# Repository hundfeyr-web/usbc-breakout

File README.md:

# USB-C to 3.3 V Breakout

A small 2-layer breakout board designed in KiCad. It takes 5 V from a USB-C port and gives a regulated 3.3 V on a 3-pin header.

This is the first design I've posted. It has not been fabricated or tested, and I don't plan to build it, so feedback on the design is welcome (see [Status](#status)).

## Features

- USB-C receptacle input (USB 2.0, 16-pin)
- 5.1 kΩ resistors on CC1 and CC2 so a USB-C charger supplies 5 V
- AP2112K-3.3 LDO regulator with input and output capacitors
- 3-pin header: +5V, +3V3, GND
- 30 x 25 mm, 2 layers, GND copper pour on both layers

## Bill of materials

| Ref | Value | Part | Qty |
|-----|-------|------|-----|
| J1 | USB-C receptacle | Palconn UTC16-G (16-pin, USB 2.0) | 1 |
| U1 | 3.3 V LDO | AP2112K-3.3 (SOT-23-5) | 1 |
| C1, C2 | 1 µF | Capacitor (C1 input, C2 output) | 2 |
| C3 | 100 nF | Output capacitor | 1 |
| R1, R2 | 5.1 kΩ | CC1 and CC2 resistors | 2 |
| J2 | 1x03 | Pin header (+5V, +3V3, GND) | 1 |

## Files

- `*.kicad_pro`, `*.kicad_sch`, `*.kicad_pcb`: KiCad project, schematic and board
- `images/`: 3D renders
  - `usbc-breakout.png`: top view
  - `2.png`: front view
  - `3.png` and `4.png`: side views
  - `5.png`: back view

## Design notes

- **Connector:** J1 is rotated 180° so its "PCB Edge" line sits on the top board edge.
- **Symbol and footprint mismatch:** my first USB-C connector symbol did not match the footprint, which caused a pile of DRC errors. Switching to the 16-pin Palconn UTC16-G symbol and footprint fixed it.
- **Ground fill:** GND zones on F.Cu and B.Cu with 0.3 mm clearance and solid pad connections. The fill left a few isolated copper islands, so I added vias to tie them back to GND.
- **Copper to hole clearance:** I lowered it to 0.2 mm in the board setup so J1's mounting pegs pass DRC. Check this against your fab's minimum before ordering. It may need to be raised or the footprint adjusted.
- **Silkscreen:** I turned off the "silkscreen clipped by board edge" DRC warning.
- **DRC:** 0 violations, 0 unrouted items.

## Status

- Schematic and layout finished, DRC clean
- Not fabricated or tested, and I don't plan to fabricate it
- Feedback on the design is welcome: please open an issue or message me

## Author

Hundaol Feyera  
[LINKEDIN_LINK](https://www.linkedin.com/in/hundaol-feyera-5a99b93a8?utm_source=share_via&utm_content=profile&utm_medium=member_android)

## License

MIT

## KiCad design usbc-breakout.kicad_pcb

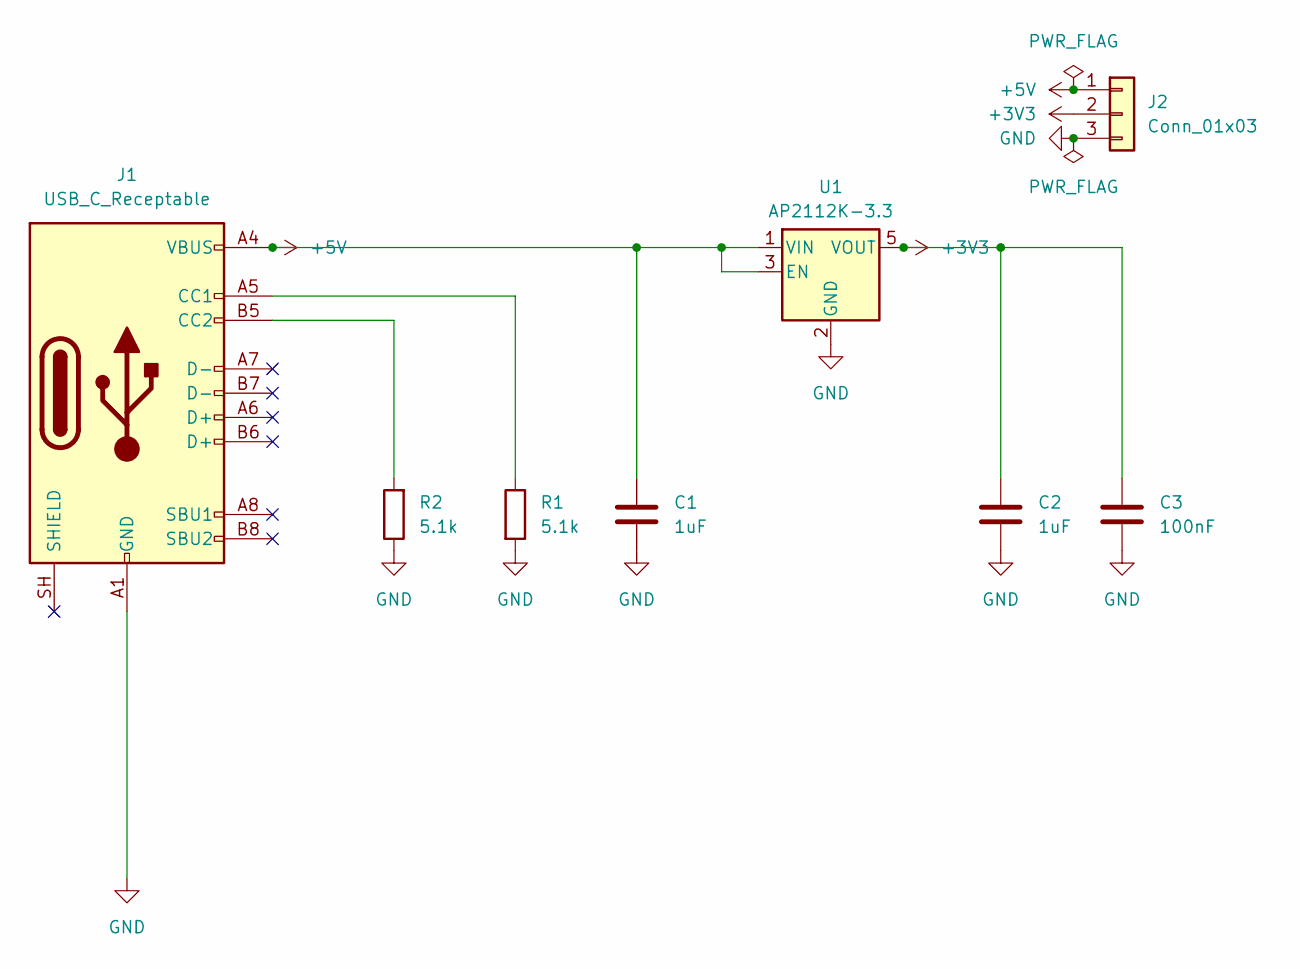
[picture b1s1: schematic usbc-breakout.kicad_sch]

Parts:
C1, C2: 1uF; C_0603_1608Metric
C3: 100nF; C_0603_1608Metric
J1: USB_C_Receptable; USB_C_Receptacle_Palconn_UTC16-G
J2: Conn_01x03; PinSocket_1x03_P2.54mm_Vertical
R1, R2: 5.1k; R_0603_1608Metric
U1: AP2112K-3.3; SOT-23-5

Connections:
+3V3: C2.1, C3.1, J2.2, U1.5 (VOUT)
+5V: C1.1, J1.A4 (VBUS), J1.A9 (VBUS), J1.B4 (VBUS), J1.B9 (VBUS), J2.1, U1.1 (VIN), U1.3 (EN)
GND: C1.2, C2.2, C3.2, J1.A1 (GND), J1.A12 (GND), J1.B1 (GND), J1.B12 (GND), J2.3, R1.2, R2.1, U1.2 (GND)
unnamed: J1.A5 (CC1), R1.1
unnamed: J1.B5 (CC2), R2.2

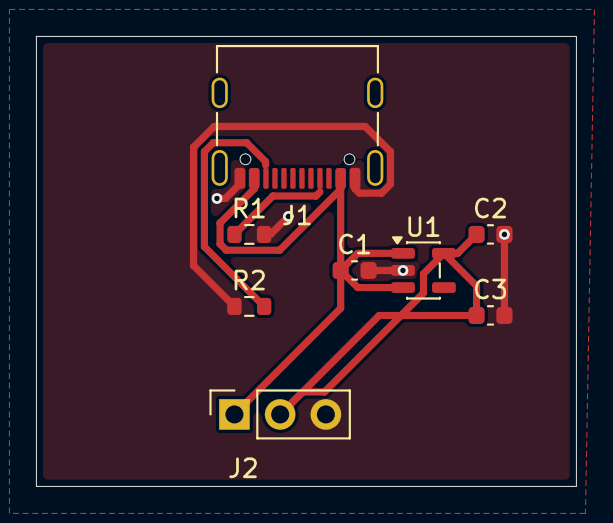
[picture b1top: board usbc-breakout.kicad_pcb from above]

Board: 2 copper layers, 30.0 x 25.0 mm, 8 parts (0 on the bottom side), 5 nets.
